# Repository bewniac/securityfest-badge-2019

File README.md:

# Security fest 2019 - n00Badge
Here you go, all the code and files that exist as a part of the official Security fest 2019 badge we call "n00Badge". First of all, you should know that I'm a complete n00b (hence the name) and this is my first ever project designing a PCB from scratch. I've learned a lot and it was a lot of fun with more headaches than I could count. I recommend everyone wanting to get into electronics to do what I did, get an idea what you want to do and then, like Nike say, Just do it!

The schematics and PCB design are all made in [KiCAD](http://kicad-pcb.org/) which is an Open Source Electrionics design suite. There's a lot of PCB footprints and schematic symbols for KiCAD and it's easy to make your own. There's other suites available but I use KiCAD because it was my first result on Google. 

I wanted to do something cool for Security fest 2019 and I wanted to do it myself from scratch. So I got my hands on my first ESP8266 board, the ESP-12F. It's a WiFi IoT thingy and can both work as an Access Point and a WiFi client and you can get it for 3 USD, or about 50 SEK if you buy it in Sweden. Now I have a WiFi capable microcontroller. But I wanted more. So I bought a Nokia 5110 LCD screen which costs about the same as the ESP-12F. This became my head requirements for the project:

  * Nokia 5110 LCD
  * ESP8266
  * Powered by micro USB

Simple enough. I built a prototype that could be powered by 5V micro USB. Although the components require 3.3V, but with a voltage regulator (LD1117V33) this wasn't an issue. The result was this:

Not so pretty, I know. But it worked. But then I wanted to create my own PCB prototype, with as much hand-solderable components as possible as I've never done SMD soldering before. I created my first schematic and PCB design in KiCAD. 

Still not pretty, but much better than my hand-made prototype and very fun to do! I ordered 10 PCBs from https://jlcpcb.com/ and the components I was missing from https://lcsc.com/ and waited. When it arrived I was extatic! My first PCB! I soldered all the components as soon as I got it (although I had to fix some errors with the backlight LEDs at first, I forget a GND route to the backlight LEDs). 

When I did some programming trying to come up with some fun stuff to add I found I was missing something, buttons for user interaction. So I had to modify the badge a bit. I used the ADC (Analog to Digital Converter) pin to add two buttons and controll them with one pin. This can be done by adding resistors of different value to the GND leg of each button. The analog voltage is converted by the pin to a digital number. The resistors will reduce the voltage to different values on each button, hence the digital number will be differ between the buttons and I can make descisions in the code based on those values. Next I had a brilliant idea, it has to be battery powered! A Li-Po battery should do the trick. But we also like to charge the Li-Po battery. So I modified my prototype by hand, added buttons, a Li-Po battery and a Li-Po charger circuit (from Adafruit, which is open hardware and the schematics are avaiable on their website). The result was this:

So now I got a prototype I feel pretty good about to work on. It runs on battery and the battery can be charged, AWESOME! Now I want to make the final design. A square badge feels so boring and we've got a cool logo to work with. So I started to create a schematic including the charging curcuit (based on the Adafruit schematic) and the buttons. And I also made some changes I replaced the ESP-12F module for the new ESP-12S module. Same form-factor, removed unnecessary pins and little faster CPU frequency. I had to edit the ESP-12F module PCB footprint myself to get a footprint for the new component. 

The final schematic:

And the final PCB design:

(Several month after, when we finally got the finished assembled PCB:s from seeedstudio)

F\*ck. Look at the through-holes for TX/RX. They're placed on top of the ESP-12S module. This is my fault, I'm sorry everybody. I've changed it in the PCB design now, but all your badges include that specific flaw. Also, I used a resistor connected to GPIO00 with a too much resistance. So you can't get the voltage low enough to get the system in flash mode (it stays in 1,4-1,7 V). Either bridge the connection or use a 1k resistor instead. Sorry about that. 

Schematic and PCB with fixed issues.

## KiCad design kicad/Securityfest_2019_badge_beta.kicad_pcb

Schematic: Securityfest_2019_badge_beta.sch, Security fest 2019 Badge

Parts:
C1, C2, C4: 10uF; C_0603_HandSoldering
C3, C5: 100nF; C_0603_HandSoldering
D1: RED_LED; LED_0603_HandSoldering
D2: GREEN_LED; LED_0603_HandSoldering
D3, D4, D5, D6: LED; LED_0603
J1: Micro_USB; USB_Micro-B_Wuerth-629105150521
J2: JST_CHARGE; JST_PH_S2B-PH-SM4-TB_02x2.00mm_Angled
J3: GPIO16; Pin_Header_Straight_1x01_Pitch1.00mm
J4: TX/RX; Pin_Header_Straight_1x02_Pitch1.00mm
R1, R5: 2k; R_0603_HandSoldering
R2, R3, R7: 470; R_0603_HandSoldering
R4, R12: 1k; R_0603_HandSoldering
R6: 220; R_0603_HandSoldering
R8, R9, R10, R11, R13, R14, R15, R16: 10k; R_0603_HandSoldering
RV1: BACKLIGHT; Trimpot_3.8mmx3.6mm_TC33X-2-103E
S1: ON/OFF; Switch_Slide_11.6x4mm_EG1218; MPN EG1218; Digi-Key_PN EG1903-ND
S2: BOOT/FLASH; Switch_Slide_11.6x4mm_EG1218; MPN EG1218; Digi-Key_PN EG1903-ND
SW1: A; SW_PUSH_6mm_h5mm
SW2: B; SW_PUSH_6mm_h5mm
SW3: RESET; SW_PUSH_6mm_h5mm
U1: MCP73831T-2ACI_OT; SOT-23-5
U2: LD1117V33; SOT-223; MPN LD1117V33; Digi-Key_PN 497-1491-5-ND
U3: Nokia_5110_LCD; Nokia_5110-3310_LCD
U4: ESP-12F; ESP-12E

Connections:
+3V3: R4.1, R5.1, R8.2, R15.1, RV1.3, S1.1, S2.1, U3.4, U3.9, U4.8 (VCC)
/3.3V: C4.2, S1.2, U2.2
GND: C1.1, C2.1, C3.1, C4.1, C5.1, D2.1, D3.1, D4.1, D5.1, D6.1, J1.5, J2.2, R1.2, R6.2, R16.1, RV1.1, S2.3, SW3.1, U1.2, U2.1, U3.3, U4.15 (GND)
unnamed: C1.2, D1.2, J1.1, U1.4
unnamed: C2.2, C3.2, J2.1, U1.3, U2.3
unnamed: C5.2, U3.2
unnamed: D1.1, R2.1
unnamed: D2.2, R3.1
unnamed: D3.2, D4.2, D5.2, D6.2, R7.1
unnamed 12: U4.4 (GPIO16); also elsewhere on the board
unnamed 13: U4.22 (TXD); also elsewhere on the board
unnamed 14: U4.21 (RXD); also elsewhere on the board
unnamed: R1.1, U1.5
unnamed: R2.2, R3.2, U1.1
unnamed: R4.2, SW1.2
unnamed: R5.2, SW2.2
unnamed: R6.1, SW1.1, SW2.1, U4.2 (ADC)
unnamed: R7.2, RV1.2
unnamed: R8.1, U4.3 (CH_PD)
unnamed: R9.1, U4.5 (GPIO14)
unnamed: R9.2, U3.8
unnamed: R10.1, U4.6 (GPIO12)
unnamed: R10.2, U3.6
unnamed: R11.1, U4.7 (GPIO13)
unnamed: R11.2, U3.7
unnamed: R12.1, U3.5
unnamed: R12.2, U4.20 (GPIO5)
unnamed: R13.1, U3.1
unnamed: R13.2, U4.19 (GPIO4)
unnamed: R14.1, S2.2
unnamed: R14.2, U4.18 (GPIO0)
unnamed: R15.2, U4.17 (GPIO2)
unnamed: R16.2, U4.16 (GPIO15)
unnamed: SW3.2, U4.1 (REST)

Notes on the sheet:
2k = 500mA Only for use with single cell Li-Ion 3.7/4.2V batteries over 500mAh

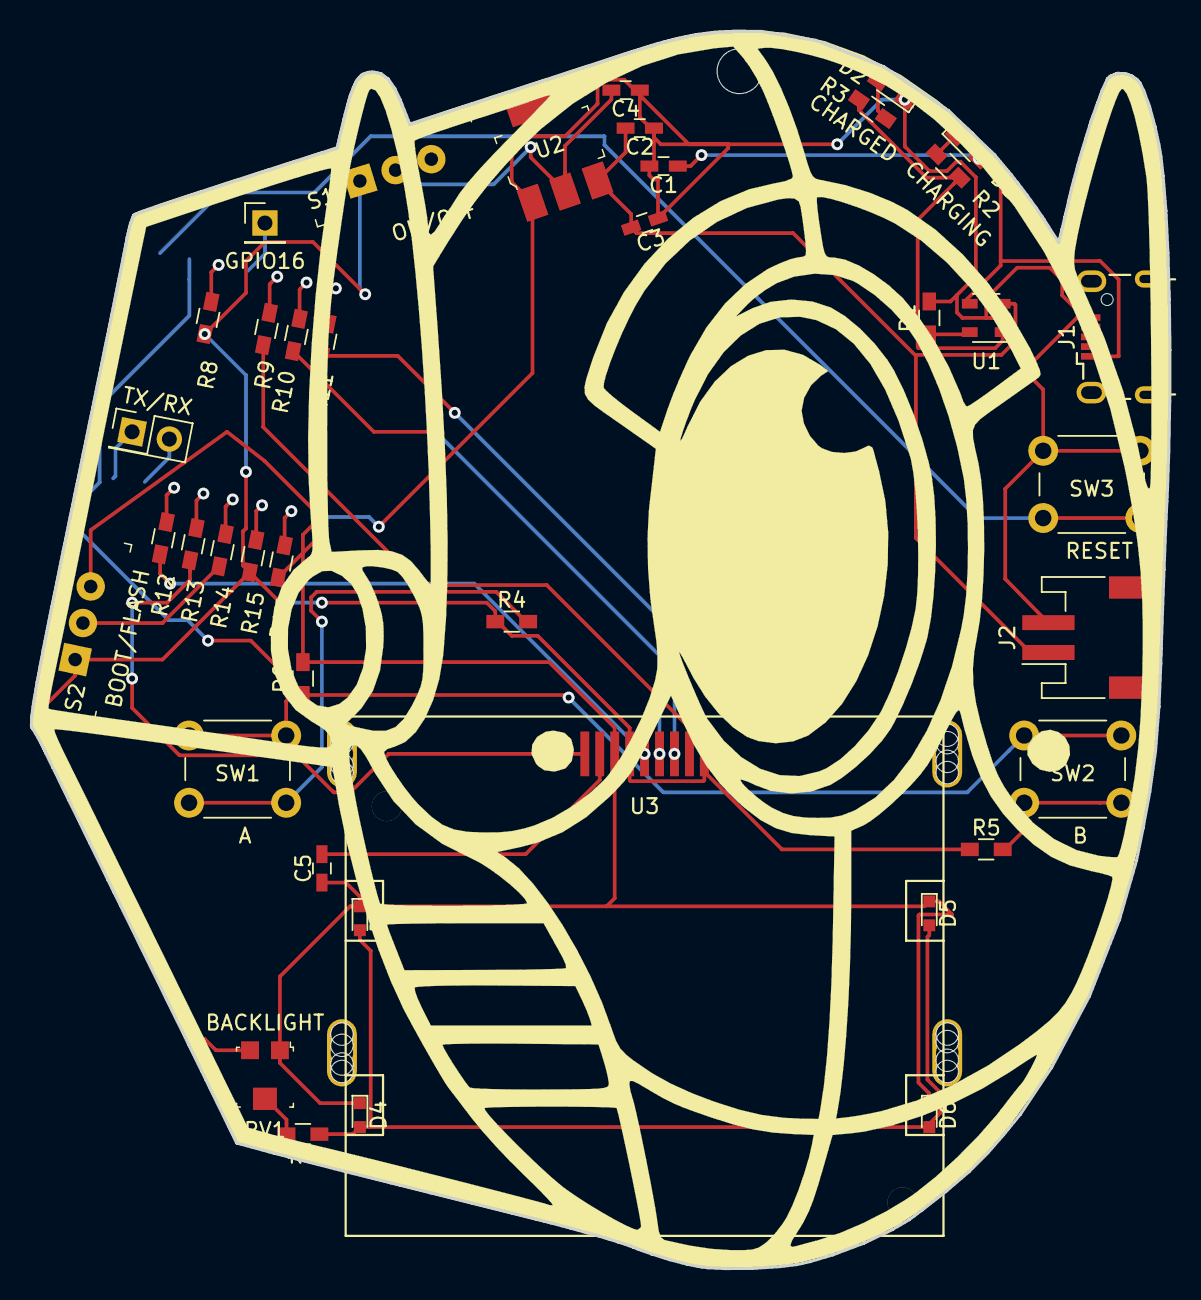
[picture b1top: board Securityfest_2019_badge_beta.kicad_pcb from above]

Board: 2 copper layers, 76.2 x 82.8 mm, 41 parts (1 on the bottom side), 34 nets.

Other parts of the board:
GPIO16: GPIO16; Pin_Header_Straight_1x01_Pitch2.54mm
TX/RX: RX/TX; Pin_Header_Straight_2x01_Pitch2.54mm

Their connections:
unnamed 12: GPIO16.1; also elsewhere on the board
unnamed 13: TX/RX.1; also elsewhere on the board
unnamed 14: TX/RX.2; also elsewhere on the board

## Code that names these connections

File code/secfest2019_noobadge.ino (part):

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#include <ESP8266HTTPUpdateServer.h>
#include <ESP8266WebServer.h>

// GPIO14 - Serial clock out (SCLK)
// GPIO13 - Serial data out (DIN)
// GPIO12 - Data/Command select (D/C)
// GPIO05 - LCD chip select (CS)
// GPIO04 - LCD reset (RST)
Adafruit_PCD8544 display = Adafruit_PCD8544(14, 13, 12, 5, 4);

int OUTPIN = 16; // GPIO16 - Free PIN
int ADC_Button = A0; // ADC - Analog digital converter pin for buttons
int LED = 2; // Onboard LED, LOW turns LED on for some reason.

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
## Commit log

2019-01-20 Moved from local git repo to github
2019-01-20 Moving images
2019-01-20 Removed redundant images
2019-01-20 Changed name of dir
2019-01-20 Removed old dir cause I'm bad at git
2019-01-20 Removed unneeded stuff
2019-02-02 added new code with challenge
2019-02-02 changed walkthrough to readme
2019-02-02 changed name to readme.md
2019-02-03 Removed old kicad files
2019-02-03 Added new kicad files
2019-02-03 Removed private stuff
2019-02-03 Re-did the menu and added helper functions. Scrolling and pages available now
2019-02-03 Made some more changes
2019-04-13 Changed name of dir, added som shit
2019-04-13 added old folder
2019-04-14 Added almost finished code
2019-04-14 I LOVE MAKING COMMITS!
2019-05-07 Added new challenge with secret which is pushed from master badge to victim badges
2019-05-09 Added challenge
2019-05-10 Fixed shit
2019-05-11 Release 0.1
2019-05-11 Release WE WILL FLASH EVERYTHING TOMORROW
2019-05-11 Added masterbadge
2019-05-18 Fixed masterbadge
2019-05-18 Removed some files
2019-05-19 Wtf?
2019-05-19 I dont understand git
2019-05-19 removed old files
2019-05-19 Removed more files
2019-05-19 Removed and added files
2019-05-19 Removed
2019-05-19 New bom
2019-05-19 Grammar
